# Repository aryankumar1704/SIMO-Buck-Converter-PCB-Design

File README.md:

# SIMO-Buck-Converter-PCB-Design
# Single-Input Multi-Output (SIMO) Buck Converter
Developed for the course **EE 396: Design Lab** at the Indian Institute of Technology (IIT), Guwahati under the supervision of Dr. Shabari Nath. This project demonstrates a synchronous **Single-Input Multi-Output (SIMO) Buck Converter** featuring complementary switching hardware, optical isolation, and digital control implemented on a Xilinx Artix-7 FPGA development board. The design replaces traditional freewheeling diodes with active synchronous switches to maximize power efficiency, time-sharing power from a common node out across three distinct output channels. Full schematics, Verilog hardware source modules, board footprints, and calculation scripts are detailed inside the project folder file bandgap_current_ref.pdf.
## Hardware Architecture & Design Parameters
The physical layout centers on a common switching hub driven by an primary power MOSFET and a synchronous rectifier switch ($U0/U\times1$) receiving complementary PWM gate signals. Downstream energy is distributed to three independent output rails via dedicated selection MOSFETs ($U1, U4, U3$) operating on a time-sharing network. Electrical isolation is maintained by feeding the digital FPGA control waveforms into high-speed HCPL3120 optocouplers powered through floating MGJ2D241509SC isolated DC-DC converters[cite: 2]. Operating from a $V_{in} = 20\text{ V}$ supply to target a $V_{out} = 10\text{ V}$ output at a $D = 0.5$ duty cycle, the power stage utilizes a calculated $560\ \mu\text{H}$ filter inductor and parallel $33\ \mu\text{F}$ electrolytic/SMD capacitor banks to split high and low-frequency noise. At a switching frequency of $f_s = 20\text{ kHz}$, theoretical calculations yield an inductor current ripple ($\Delta I_l$) of $\approx 0.45\text{ A}$ and a tight output voltage ripple ($\Delta V_{out}$) of $\approx 84.5\text{ mV}$.
## FPGA Pulse Control & Experimental Results
The control architecture is written in Verilog and targeted to a Digilent Nexys A7 100T FPGA board. Synchronous switching logic runs on an internal FSM counter that scales the native $100\text{ MHz}$ oscillator to $20\text{ kHz}$, enabling user-controlled toggling between $30\%$ and $50\%$ duty cycles using debounced mechanical input buttons. To guarantee safety and prevent destructive shoot-through current across the half-bridge, the Verilog code implements a strict hardware dead-time window of $200$ clock cycles, creating a $2\ \mu\text{s}$ delay where both control signals remain low. Bench testing validated the design via Tektronix and Keysight digital oscilloscopes. The recorded current and voltage waveforms confirm stable, continuous conduction mode (CCM) operation with ripple dynamics matching theoretical models, proving the viability of this FPGA-driven SIMO matrix for multi-rail power applications.

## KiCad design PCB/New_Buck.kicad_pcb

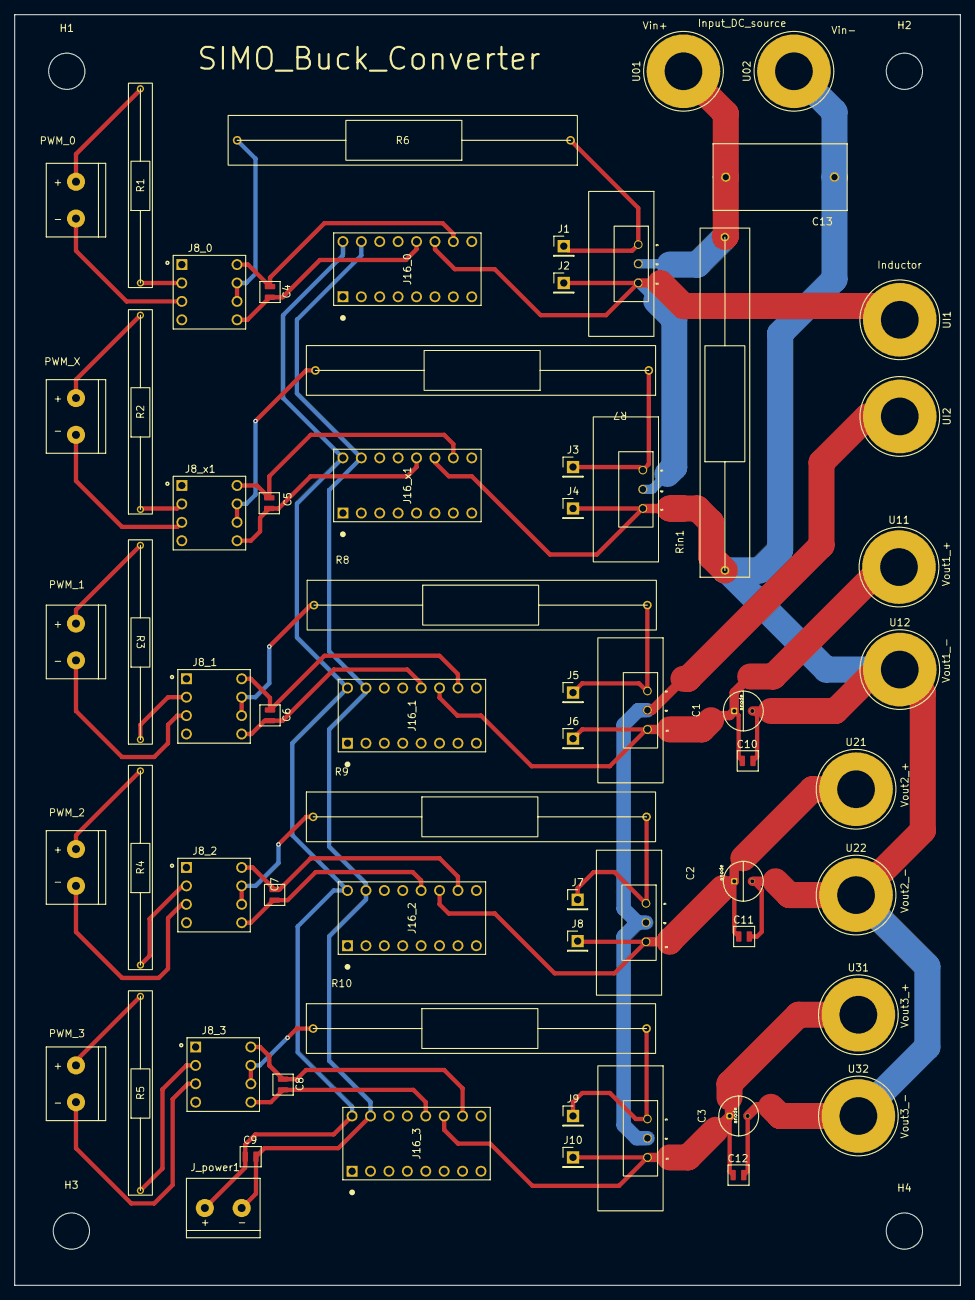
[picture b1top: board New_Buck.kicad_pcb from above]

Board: 2 copper layers, 130.5 x 175.3 mm, 69 parts (0 on the bottom side), 44 nets.

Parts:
C1, C2, C3: 33uf; MCKSK050M330D11S
C4: 0.1 uf; C0805C104K5RACTU
C5, C6, C7, C8, C9, C10, C11, C12: C_Small_US; C0805C104K5RACTU
C13: R46KI347050P1M; CAPRR1500W60L1850T920H1260
H1, H2, H3, H4: MountingHole; MountingHole_5mm
J1, J2, J3, J4, J5, J6, J7, J8, J9, J10: Conn_01x01_Pin; PinHeader_1x01_P2.54mm_Vertical
J8_0, J8_1, J8_2, J8_3, J8_x1: 1-2199298-2; TE_1-2199298-2
J16_0, J16_1, J16_2, J16_3, J16_x1: 1-2199298-4; TE_1-2199298-4
J_power1: 282837-2; TE_282837-2
P0, P1, P2, P3: 282837-2; TE_282837-2
Px1: 282837-2; TE_282837-2
R1, R2, R3: 220ohm; CFR-25JT-52-220R
R4, R5: 220 ohm; CFR-25JT-52-220R
R6, R7, R8, R9, R10: 10 ohm; ROX3SJ10R
Rin1: 10 ohm; ROX3SJ10R
U0: STP55NF06; STP55NF06_nchannel_mosfet
U01, U02, U11, U12, U21, U22, U31, U32: Banana_Jack_1Pin_4mm
U1, U3, U4: STP55NF06L; STP55NF06_nchannel_mosfet
UI1, UI2: Banana_Jack_1Pin_4mm
Ux1: STP55NF06L; STP55NF06_nchannel_mosfet

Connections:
unnamed: C4.1, J8_0.8, J16_0.10
unnamed: C4.2, J8_0.5, J16_0.12
unnamed: C5.1, J8_x1.8, J16_x1.10
unnamed: C5.2, J8_x1.5, J16_x1.12
unnamed: C6.1, J8_1.8, J16_1.10
unnamed: C6.2, J8_1.5, J16_1.12
unnamed: C7.1, J8_2.8, J16_2.10
unnamed: C7.2, J8_2.5, J16_2.12
unnamed: C8.1, J8_3.8, J16_3.10
unnamed: C8.2, J8_3.5, J16_3.12
unnamed: J8_0.2, R1.1
unnamed: J8_0.3, P0.1
unnamed: J8_0.6, J8_0.7, R6.2
unnamed: J8_1.2, R3.1
unnamed: J8_1.3, P1.1
unnamed: J8_1.6, J8_1.7, R8.1
unnamed: J8_2.2, R4.1
unnamed: J8_2.3, P2.1
unnamed: J8_2.6, J8_2.7, R9.1
unnamed: J8_3.2, R5.1
unnamed: J8_3.3, P3.1
unnamed: J8_3.6, J8_3.7, R10.1
unnamed: J8_x1.2, R2.1
unnamed: J8_x1.3, Px1.1
unnamed: J8_x1.6, J8_x1.7, R7.2
unnamed: P0.2, R1.2
unnamed: P1.2, R3.2
unnamed: P2.2, R4.2
unnamed: P3.2, R5.2
unnamed: Px1.2, R2.2
unnamed: C13.2, Rin1.2, U0.2, U01.1 (banana_pin)
unnamed: U1.2, U3.2, U4.2, UI2.1 (banana_pin)
Vin+: C9.1, J16_0.16, J16_1.16, J16_2.16, J16_3.16, J16_x1.16, J_power1.1
Vin-: C9.2, J16_0.15, J16_1.15, J16_2.15, J16_3.15, J16_x1.15, J_power1.2
gate_0: J1.1, R6.1, U0.1
gate_1: J5.1, R8.2, U1.1
gate_2: J7.1, R9.2, U4.1
gate_3: J9.1, R10.2, U3.1
gate_x: J3.1, R7.1, Ux1.1
source_0: J2.1, J16_0.11, U0.3, UI1.1 (banana_pin), Ux1.2
source_1: C1.1, C10.1, J6.1, J16_1.11, U1.3, U11.1 (banana_pin)
source_2: C2.1, C11.1, J8.1, J16_2.11, U4.3, U21.1 (banana_pin)
source_3: C3.1, C12.1, J10.1, J16_3.11, U3.3, U31.1 (banana_pin)
source_x: C1.2, C2.2, C3.2, C10.2, C11.2, C12.2, C13.1, J4.1, J16_x1.11, Rin1.1, U02.1 (banana_pin), U12.1 (banana_pin), U22.1 (banana_pin), U32.1 (banana_pin), Ux1.3

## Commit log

2026-05-24 Add image to README for SIMO Buck Converter project
2026-05-24 Enhance README with project details and results
    Expanded project description with detailed hardware architecture, design parameters, and FPGA control information.
2026-05-27 Create PCB
2026-05-28 Create file
